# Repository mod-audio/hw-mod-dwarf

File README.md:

# hw-mod-dwarf

This repository contains the schematics and PCB design files for the MOD Dwarf hardware.

These files were created and can be improved with KiCAD, a free software Electronics CAD which is available at http://www.kicad.org/

This project should work with last revision of KiCad libraries and footprints available at https://github.com/KiCad/

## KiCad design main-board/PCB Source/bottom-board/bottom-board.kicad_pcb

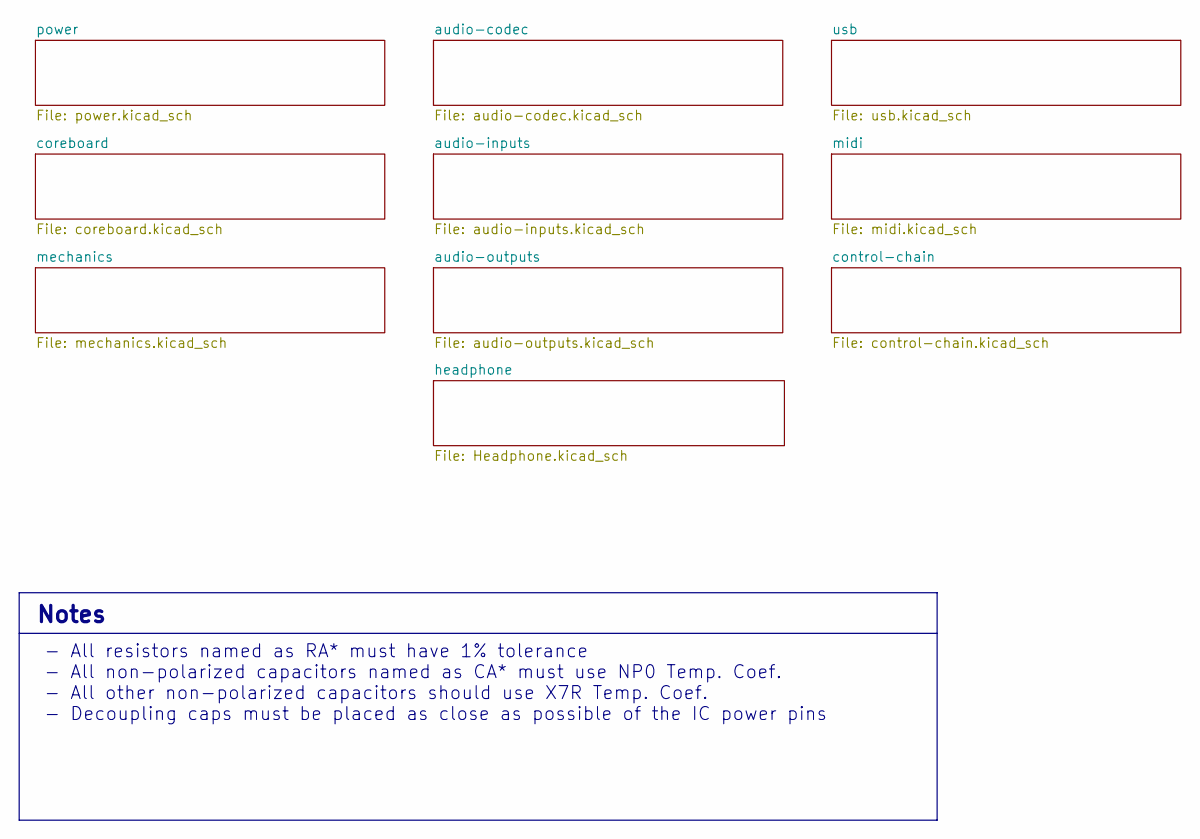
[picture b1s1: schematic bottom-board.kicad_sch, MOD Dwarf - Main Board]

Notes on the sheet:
- All resistors named as RA* must have 1% tolerance - All non-polarized capacitors named as CA* must use NP0 Temp. Coef. - All other non-polarized capacitors should use X7R Temp. Coef. - Decoupling caps must be placed as close as possible of the IC power pins
Notes

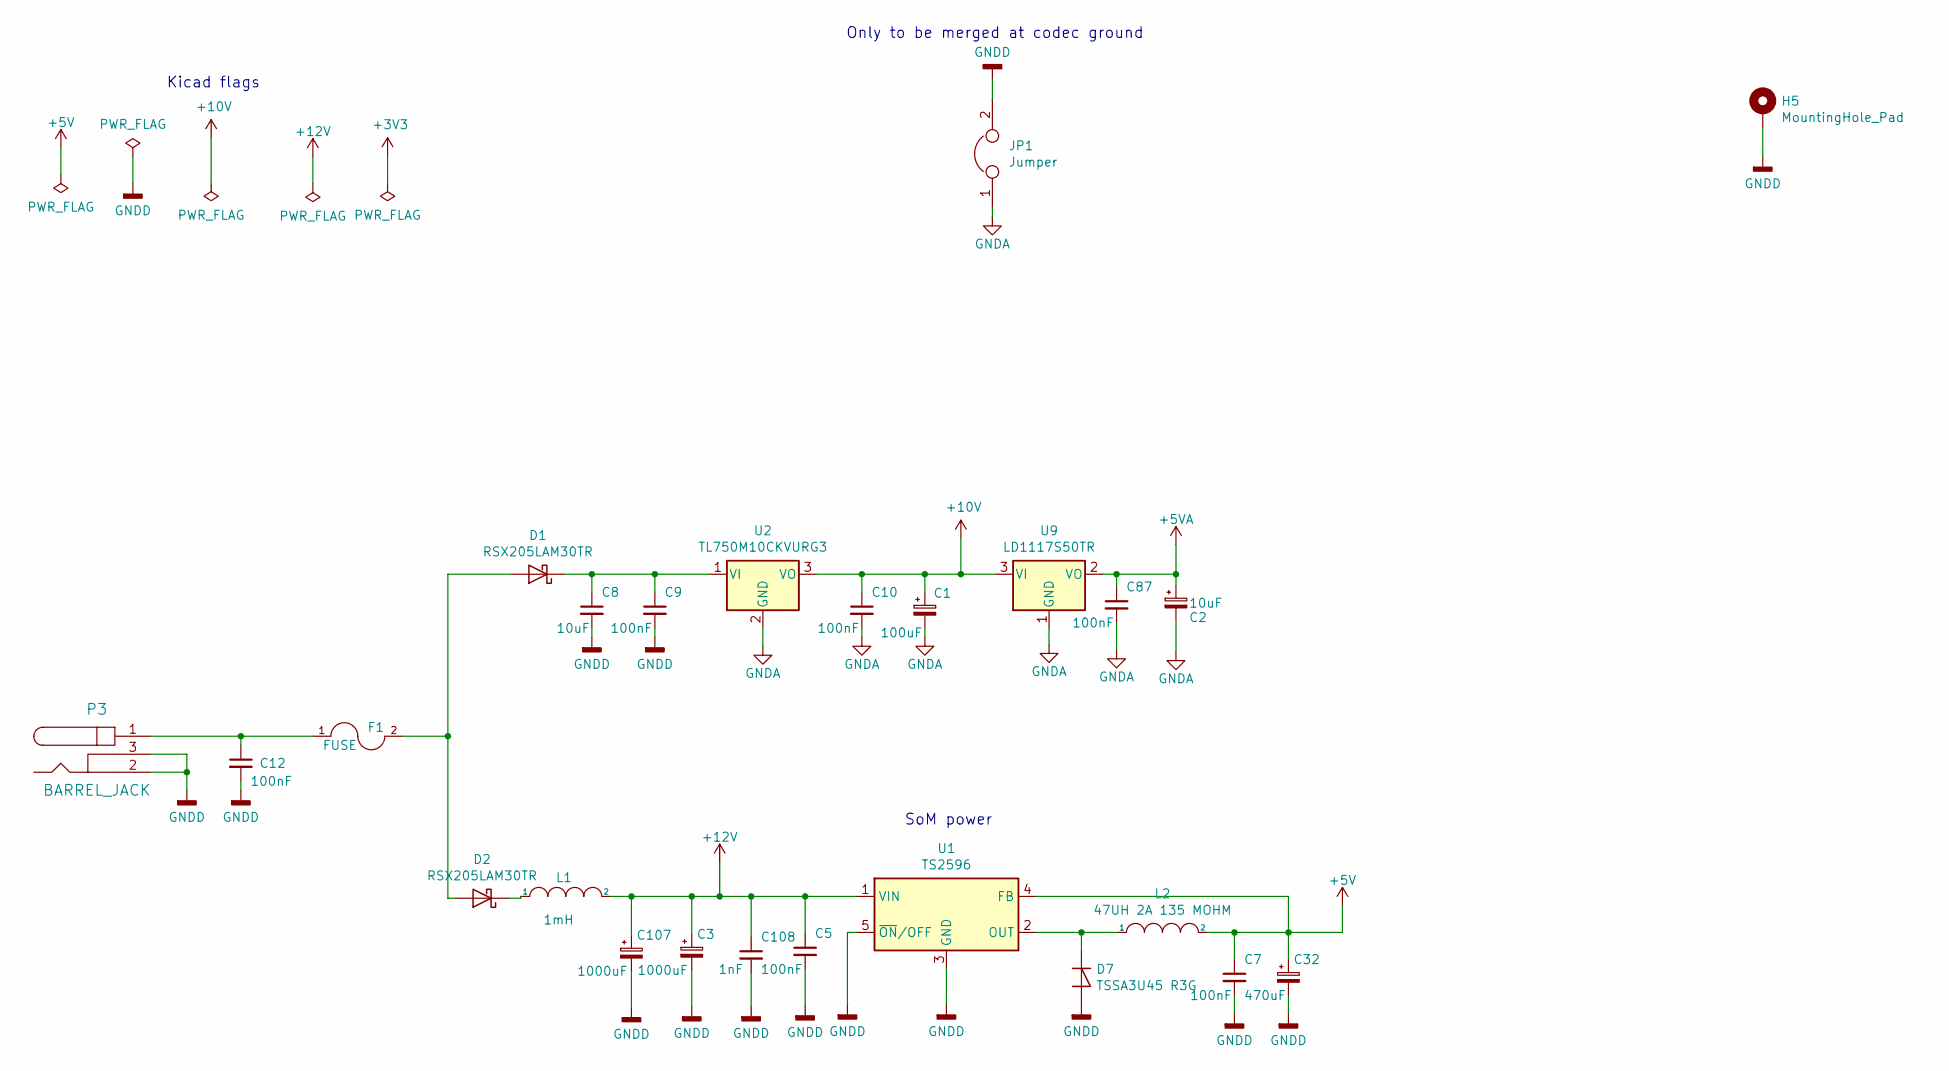
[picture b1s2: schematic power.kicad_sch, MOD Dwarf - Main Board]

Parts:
C1: 100uF; CP_Elec_6.3x7.7; MPN 107SML016M
C2: 10uF; CP_Elec_4x5.7; MPN EEE-HB1C100R
C3, C107: 1000uF; CP_Elec_10x10.5; MPN UCM1C102MNL1GS
C5, C7, C9, C10, C12, C87: 100nF; C_0603_1608Metric; MPN GCM188R71C104KA37D
C8: 10uF; C_0805_2012Metric; MPN GRM219R61E106KA12D
C32: 470uF; CP_Elec_8x10.5; MPN UCW1C471MNL1GS
C108: 1nF; C_0603_1608Metric; MPN C0603X7R500-103KNP
D1, D2: RSX205LAM30TR; D_SOD-128; MPN RSX205LAM30TR
D7: TSSA3U45 R3G; D_MELF; MPN TSSA3U45 R3G
F1: FUSE; Fuse_2920_7451Metric; MPN 0ZCF0200FF2C
H5: MountingHole_Pad; MountingHole_3.2mm_M3_DIN965_Pad
JP1: Jumper; SolderJumper-2_P1.3mm_Bridged2Bar_RoundedPad1.0x1.5mm
L1: 1mH; L_Bourns_SRR1260; MPN SRR1260-102K
L2: 47UH 2A 135 MOHM; SRN8040TA; MPN SRN8040TA-470M
P3: BARREL_JACK; BarrelJack_Horizontal; MPN PJ-002AH
U1: TS2596; TO-263-5_TabPin3; MPN TS2596CM550 RNG
U2: TL750M10CKVURG3; TO-252-3_TabPin2; MPN TL750M10CKVURG3
U9: LD1117S50TR; SOT-223-3_TabPin2; MPN LD1117S50TR

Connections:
+5V: C7.1, C32.1, L2.2, U1.4 (FB); also elsewhere on the board
+5VA: C2.1, C87.1, U9.2 (VO); also elsewhere on the board
+10V: C1.1, C10.1, U2.3 (VO), U9.3 (VI); also elsewhere on the board
+12V: C3.1, C5.1, C107.1, C108.1, L1.2, U1.1 (VIN); also elsewhere on the board
GNDA: C1.2, C2.2, C10.2, C87.2, JP1.1, U2.2 (GND), U9.1 (GND); also elsewhere on the board
GNDD: C3.2, C5.2, C7.2, C8.2, C9.2, C12.2, C32.2, C107.2, C108.2, D7.2 (A), H5.1, JP1.2, P3.2, P3.3, U1.3 (GND), U1.5 (~ON/OFF); also elsewhere on the board
unnamed: C8.1, C9.1, D1.1 (K), U2.1 (VI)
unnamed: C12.1, F1.1, P3.1
unnamed: D1.2 (A), D2.2 (A), F1.2
unnamed: D2.1 (K), L1.1
unnamed: D7.1 (K), L2.1, U1.2 (OUT)

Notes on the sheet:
SoM power
Only to be merged at codec ground
Kicad flags

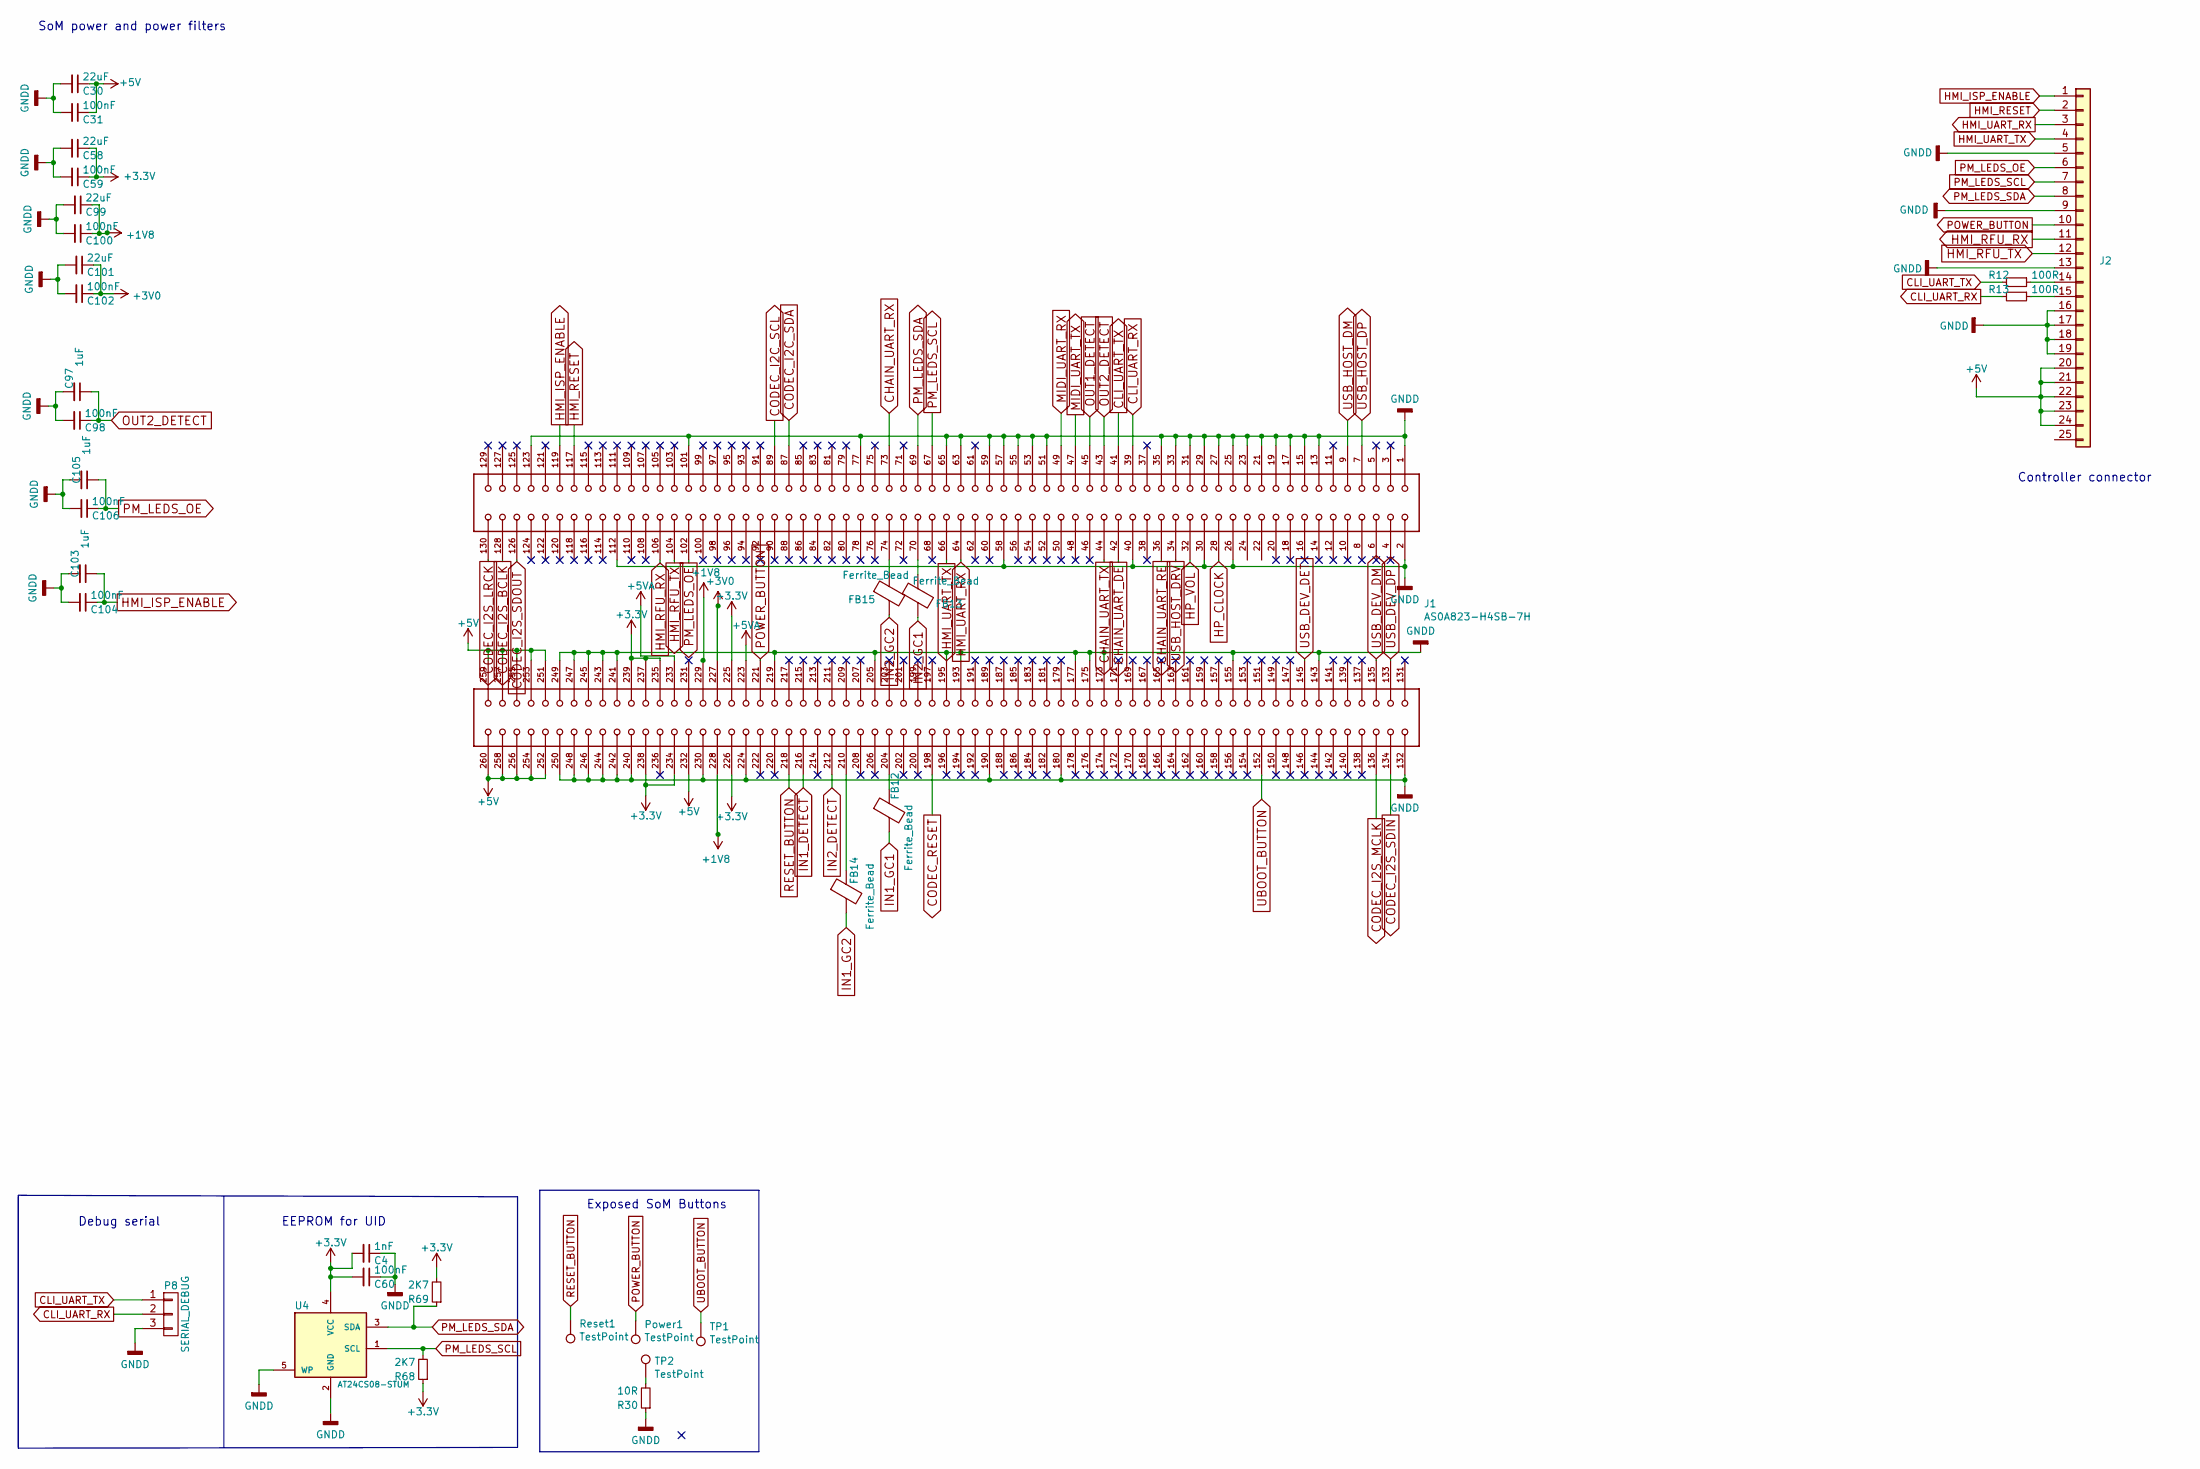
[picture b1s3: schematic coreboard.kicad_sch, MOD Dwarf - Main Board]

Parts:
C4: 1nF; C_0603_1608Metric; MPN C0603X7R500-103KNP
C30, C58, C99, C101: 22uF; C_0805_2012Metric; MPN CL21A226MPQNNNE
C31, C59, C60, C98, C100, C102, C104, C106: 100nF; C_0603_1608Metric; MPN GCM188R71C104KA37D
C97, C103, C105: 1uF; C_0603_1608Metric; MPN TMK107B7105KA-T
FB12, FB13, FB14, FB15: Ferrite_Bead; R_0603_1608Metric; MPN BLM18HD102SH1D
J1: AS0A823-H4SB-7H; TE_2309409-1; MPN TE_2309409-1
J2: MPN F51L-1A7H1-11024
P8: SERIAL_DEBUG; PinHeader_1x03_P2.54mm_Vertical; MPN DO NOT PLACE
Power1: TestPoint; TestPoint_Pad_D1.5mm
R12, R13: 100R; R_0603_1608Metric; MPN RT0603DRD07100RL
R30: 10R; R_0603_1608Metric; MPN CRGCQ0603J10R
R68, R69: 2K7; R_0603_1608Metric; MPN CRGCQ0603F2K7
Reset1: TestPoint; TestPoint_Pad_D1.5mm
TP1, TP2: TestPoint; TestPoint_Loop_D1.80mm_Drill1.0mm_Beaded
U4: AT24CS08-STUM; SOT-23-5; MPN AT24CS08-STUM

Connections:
+1V8: C99.1, C100.1, J1.228, J1.229
+3V0: C101.1, C102.1, J1.227
+5V: C30.1, C31.1, J1.232, J1.251, J1.252, J1.253, J1.254, J1.255, J1.256, J1.257, J1.258, J1.259, J1.260, J2.20, J2.21, J2.22, J2.23, J2.24; also elsewhere on the board
+5VA: J1.223, J1.233; also elsewhere on the board
CHAIN_UART_DE: J1.42; also elsewhere on the board
CHAIN_UART_RE: J1.36; also elsewhere on the board
CHAIN_UART_RX: J1.73; also elsewhere on the board
CHAIN_UART_TX: J1.44; also elsewhere on the board
CLI_UART_RX: J1.39, P8.2, R13.2
CLI_UART_TX: J1.41, P8.1, R12.2
CODEC_I2C_SCL: J1.89; also elsewhere on the board
CODEC_I2C_SDA: J1.87; also elsewhere on the board
CODEC_I2S_BCLK: J1.128; also elsewhere on the board
CODEC_I2S_LRCK: J1.130; also elsewhere on the board
CODEC_I2S_MCLK: J1.136; also elsewhere on the board
CODEC_I2S_SDIN: J1.134; also elsewhere on the board
CODEC_I2S_SDOUT: J1.126; also elsewhere on the board
CODEC_RESET: J1.198; also elsewhere on the board
GNDD: C4.1, C30.2, C31.2, C58.2, C59.2, C60.1, C97.2, C98.2, C99.2, C100.2, C101.2, C102.2, C103.2, C104.2, C105.2, C106.2, J1.1, J1.2, J1.13, J1.15, J1.17, J1.19, J1.21, J1.23, J1.25, J1.26, J1.27, J1.29, J1.30, J1.31, J1.33, J1.35, J1.40, J1.51, J1.53, J1.55, J1.57, J1.58, J1.59, J1.63, J1.65, J1.77, J1.101, J1.112, J1.123, J1.132, J1.143, J1.155, J1.173, J1.175, J1.177, J1.180, J1.190, J1.193, J1.195, J1.205, J1.219, J1.224, J1.230, J1.240, J1.241, J1.242, J1.243, J1.244, J1.245, J1.246, J1.247, J1.248, J1.249, J1.250, J2.5, J2.9, J2.13, J2.16, J2.17, J2.18, J2.19, P8.3, R30.1, U4.2 (GND), U4.5 (WP); also elsewhere on the board
HMI_ISP_ENABLE: C103.1, C104.1, J1.119, J2.1; also elsewhere on the board
HMI_RESET: J1.117, J2.2; also elsewhere on the board
HMI_RFU_RX: J1.106, J2.11; also elsewhere on the board
HMI_RFU_TX: J1.104, J2.12; also elsewhere on the board
HMI_UART_RX: J1.64, J2.3; also elsewhere on the board
HMI_UART_TX: J1.66, J2.4; also elsewhere on the board
HP_CLOCK: J1.28; also elsewhere on the board
HP_VOL: J1.32; also elsewhere on the board
IN1_DETECT: J1.216; also elsewhere on the board
IN1_GC1: FB12.2; also elsewhere on the board
IN1_GC2: FB14.2; also elsewhere on the board
IN2_DETECT: J1.212; also elsewhere on the board
IN2_GC1: FB13.2; also elsewhere on the board
IN2_GC2: FB15.2; also elsewhere on the board
MIDI_UART_RX: J1.49; also elsewhere on the board
MIDI_UART_TX: J1.47; also elsewhere on the board
unnamed: FB12.1, J1.204
unnamed: FB13.1, J1.70
unnamed: FB14.1, J1.210
unnamed: FB15.1, J1.74
unnamed 122: J2.14, R12.1; also elsewhere on the board
unnamed 123: J2.15, R13.1; also elsewhere on the board
unnamed: R30.2, TP2.1
OUT1_DETECT: J1.45; also elsewhere on the board
OUT2_DETECT: C97.1, C98.1, J1.43; also elsewhere on the board
PM_LEDS_OE: C105.1, C106.1, J1.102, J2.6; also elsewhere on the board
PM_LEDS_SCL: J1.67, J2.7, R68.2, U4.1 (SCL); also elsewhere on the board
PM_LEDS_SDA: J1.69, J2.8, R69.1, U4.3 (SDA); also elsewhere on the board
POWER_BUTTON: J1.221, J2.10, Power1.1; also elsewhere on the board
RESET_BUTTON: J1.218, Reset1.1; also elsewhere on the board
UBOOT_BUTTON: J1.152, TP1.1
USB_DEV_DET: J1.145; also elsewhere on the board
USB_DEV_DM: J1.135; also elsewhere on the board
USB_DEV_DP: J1.133; also elsewhere on the board
USB_HOST_DM: J1.9; also elsewhere on the board
USB_HOST_DP: J1.7; also elsewhere on the board
USB_HOST_DRV: J1.34; also elsewhere on the board

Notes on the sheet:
SoM power and power filters
Debug serial
Exposed SoM Buttons
EEPROM for UID
Controller connector

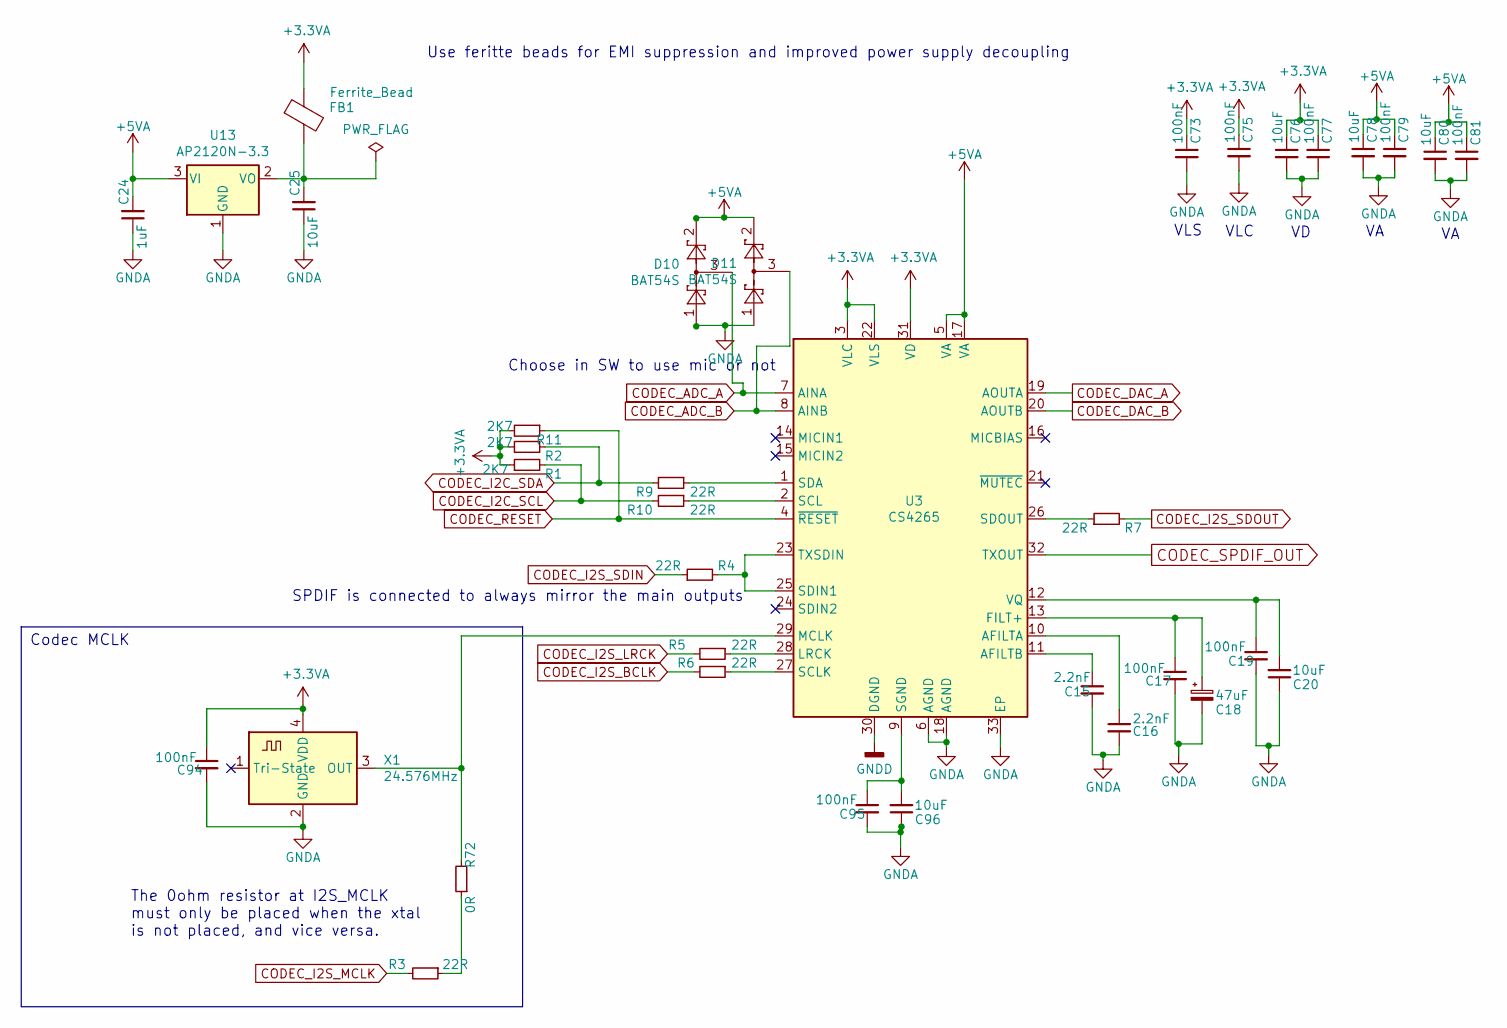
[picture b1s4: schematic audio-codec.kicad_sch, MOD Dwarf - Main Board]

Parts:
C15, C16: 2.2nF; C_0603_1608Metric; MPN GRM1885C1H222JA01D
C17, C19, C73, C75, C77, C79, C81, C94, C95: 100nF; C_0603_1608Metric; MPN GCM188R71C104KA37D
C18: 47uF; CP_Elec_5x5.4; MPN EDK476M016A9DAA
C20, C25, C76, C78, C80, C96: 10uF; C_0805_2012Metric; MPN GRM219R61E106KA12D
C24: 1uF; C_0603_1608Metric; MPN TMK107B7105KA-T
D10, D11: BAT54S; SOT-23; MPN BAT54SFILM
FB1: Ferrite_Bead; R_0603_1608Metric; MPN BLM18HD102SH1D
R1, R2, R11: 2K7; R_0603_1608Metric; MPN CRGCQ0603F2K7
R3, R4, R5, R6, R7, R9, R10: 22R; R_0603_1608Metric; MPN RMCF0603JT22R0
R72: 0R; R_0603_1608Metric; MPN RMCF0603ZT0R00
U3: CS4265; QFN-32-1EP_5x5mm_P0.5mm_EP3.1x3.1mm; MPN CS4265-CNZ
U13: AP2120N-3.3; SOT-23; MPN AP2120N-3.3TRG1
X1: 24.576MHz; Oscillator_SMD_Abracon_ASV-4Pin_7.0x5.1mm; MPN DO NOT PLACE

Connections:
+3.3VA: C73.1, C75.1, C76.1, C77.1, C94.1, FB1.1, R1.1, R2.2, R11.2, U3.3 (VLC), U3.22 (VLS), U3.31 (VD), X1.4 (VDD)
+5VA: C24.2, C78.1, C79.1, C80.1, C81.1, D10.2, D11.2, U3.5 (VA), U3.17 (VA), U13.3 (VI); also elsewhere on the board
CODEC_ADC_A: D10.3, U3.7 (AINA); also elsewhere on the board
CODEC_ADC_B: D11.3, U3.8 (AINB); also elsewhere on the board
CODEC_DAC_A: U3.19 (AOUTA); also elsewhere on the board
CODEC_DAC_B: U3.20 (AOUTB); also elsewhere on the board
CODEC_I2C_SCL: R1.2, R10.2; also elsewhere on the board
CODEC_I2C_SDA: R2.1, R9.2; also elsewhere on the board
CODEC_I2S_BCLK: R6.2; also elsewhere on the board
CODEC_I2S_LRCK: R5.2; also elsewhere on the board
CODEC_I2S_MCLK: R3.2; also elsewhere on the board
CODEC_I2S_SDIN: R4.1; also elsewhere on the board
CODEC_I2S_SDOUT: R7.2; also elsewhere on the board
CODEC_RESET: R11.1, U3.4 (~RESET); also elsewhere on the board
GNDA: C15.2, C16.2, C17.2, C18.2, C19.2, C20.1, C24.1, C25.1, C73.2, C75.2, C76.2, C77.2, C78.2, C79.2, C80.2, C81.2, C94.2, C95.2, C96.1, D10.1, D11.1, U3.6 (AGND), U3.18 (AGND), U3.33 (EP), U13.1 (GND), X1.2 (GND); also elsewhere on the board
GNDD: U3.30 (DGND); also elsewhere on the board
unnamed: C15.1, U3.11 (AFILTB)
unnamed: C16.1, U3.10 (AFILTA)
unnamed: C17.1, C18.1, U3.13 (FILT+)
unnamed: C19.1, C20.2, U3.12 (VQ)
unnamed: C25.2, FB1.2, U13.2 (VO)
unnamed: C95.1, C96.2, U3.9 (SGND)
unnamed: R3.1, R72.1
unnamed: R4.2, U3.23 (TXSDIN), U3.25 (SDIN1)
unnamed: R5.1, U3.28 (LRCK)
unnamed: R6.1, U3.27 (SCLK)
unnamed: R7.1, U3.26 (SDOUT)
unnamed: R9.1, U3.1 (SDA)
unnamed: R10.1, U3.2 (SCL)
unnamed: R72.2, U3.29 (MCLK), X1.3 (OUT)

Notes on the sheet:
Use feritte beads for EMI suppression and improved power supply decoupling
VLS
Choose in SW to use mic or not
Codec MCLK
VLC
SPDIF is connected to always mirror the main outputs
The 0ohm resistor at I2S_MCLK must only be placed when the xtal is not placed, and vice versa.

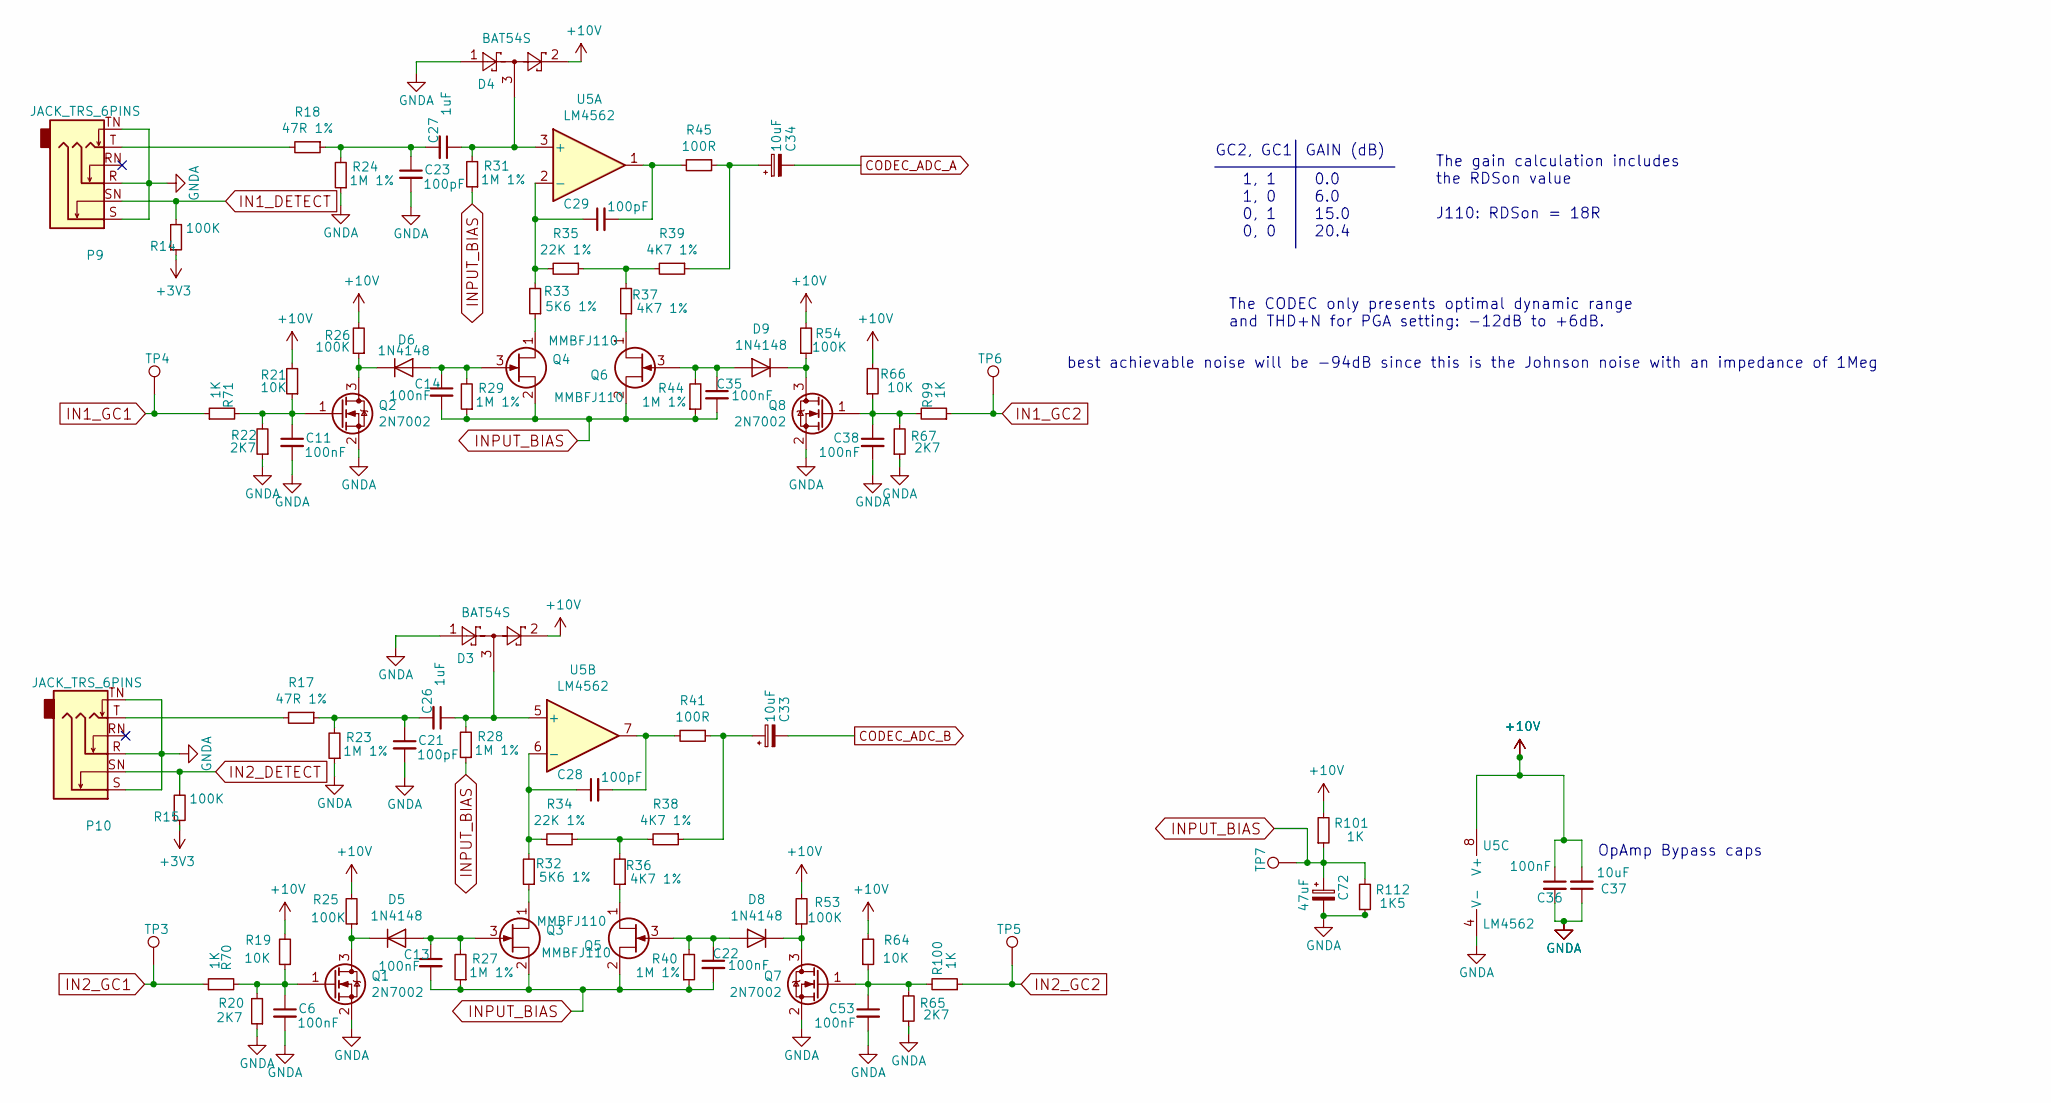
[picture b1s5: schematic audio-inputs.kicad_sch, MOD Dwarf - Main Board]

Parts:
C6, C11, C13, C14, C22, C35, C36, C38, C53: 100nF; C_0603_1608Metric; MPN GCM188R71C104KA37D
C21, C23, C28, C29: 100pF; C_0603_1608Metric; MPN C0603C101J3GACTU
C26, C27: 1uF; C_0603_1608Metric; MPN TMK107B7105KA-T
C33, C34: 10uF; CP_Elec_4x5.7; MPN EEE-HB1C100R
C37: 10uF; C_0805_2012Metric; MPN GRM219R61E106KA12D
C72: 47uF; CP_Elec_5x5.4; MPN EDK476M016A9DAA
D3, D4: BAT54S; SOT-23; MPN BAT54SFILM
D5, D6, D8, D9: 1N4148; D_SOD-323; MPN 1N4148WS
P9, P10: JACK_TRS_6PINS; Jack_3.5mm_Neutrik_NMJ6HCD2_Horizontal; MPN NYS215
Q1, Q2, Q7, Q8: 2N7002; SOT-23; MPN 2N7002P,215
Q3, Q4, Q5, Q6: MMBFJ110; SOT-23; MPN MMBFJ110
R14, R15, R25, R26, R53, R54: 100K; R_0603_1608Metric; MPN RMCF0603JT100K
R17, R18: 47R 1%; R_0603_1608Metric; MPN RT0603DRE0747RL
R19, R21, R64, R66: 10K; R_0603_1608Metric; MPN RR0816P-103-D
R20, R22, R65, R67: 2K7; R_0603_1608Metric; MPN CRGCQ0603F2K7
R23, R24, R27, R28, R29, R31, R40, R44: 1M 1%; R_0603_1608Metric; MPN RT0603BRD071ML
R32, R33: 5K6 1%; R_0603_1608Metric; MPN ERA-3AED562V
R34, R35: 22K 1%; R_0603_1608Metric; MPN RT0603DRD0722KL
R36, R37, R38, R39: 4K7 1%; R_0603_1608Metric; MPN RT0603DRE074K7L
R41, R45: 100R; R_0603_1608Metric; MPN RT0603DRD07100RL
R70, R71, R99, R100, R101: 1K; R_0603_1608Metric; MPN ERJ-PB3D1001V
R112: 1K5; R_0603_1608Metric
TP3, TP4, TP5, TP6: TestPoint; TestPoint_Pad_D1.0mm
TP7: TestPoint; TestPoint_Pad_D2.0mm
U5: LM4562; SOIC-8_3.9x4.9mm_P1.27mm; MPN LM4562MAX/NOPB

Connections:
+10V: C36.1, C37.2, D3.2, D4.2, R19.2, R21.2, R25.2, R26.2, R53.2, R54.2, R64.2, R66.2, R101.2, U5.8 (V+); also elsewhere on the board
CODEC_ADC_A: C34.2; also elsewhere on the board
CODEC_ADC_B: C33.2; also elsewhere on the board
GNDA: C6.2, C11.2, C21.2, C23.2, C36.2, C37.1, C38.2, C53.2, C72.2, D3.1, D4.1, P9.R, P9.S, P9.TN, P10.R, P10.S, P10.TN, Q1.2 (S), Q2.2 (S), Q7.2 (S), Q8.2 (S), R20.1, R22.1, R23.1, R24.1, R65.1, R67.1, R112.1, U5.4 (V-); also elsewhere on the board
IN1_DETECT: P9.SN, R14.2; also elsewhere on the board
IN1_GC1: R71.1, TP4.1; also elsewhere on the board
IN1_GC2: R99.1, TP6.1; also elsewhere on the board
IN2_DETECT: P10.SN, R15.2; also elsewhere on the board
IN2_GC1: R70.1, TP3.1; also elsewhere on the board
IN2_GC2: R100.1, TP5.1; also elsewhere on the board
INPUT_BIAS: C13.2, C14.2, C22.2, C35.2, C72.1, Q3.2 (S), Q4.2 (S), Q5.2 (S), Q6.2 (S), R27.1, R28.1, R29.1, R31.1, R40.1, R44.1, R101.1, R112.2, TP7.1
unnamed: C6.1, Q1.1 (G), R19.1, R20.2, R70.2
unnamed: C11.1, Q2.1 (G), R21.1, R22.2, R71.2
unnamed: C13.1, D5.2 (A), Q3.3 (G), R27.2
unnamed: C14.1, D6.2 (A), Q4.3 (G), R29.2
unnamed: C21.1, C26.2, R17.1, R23.2
unnamed: C22.1, D8.2 (A), Q5.3 (G), R40.2
unnamed: C23.1, C27.2, R18.1, R24.2
unnamed: C26.1, D3.3, R28.2, U5.5 (+)
unnamed: C27.1, D4.3, R31.2, U5.3 (+)
unnamed: C28.1, R32.2, R34.2, U5.6 (-)
unnamed: C28.2, R41.2, U5.7
unnamed: C29.1, R33.2, R35.2, U5.2 (-)
unnamed: C29.2, R45.2, U5.1
unnamed: C33.1, R38.1, R41.1
unnamed: C34.1, R39.1, R45.1
unnamed: C35.1, D9.2 (A), Q6.3 (G), R44.2
unnamed: C38.1, Q8.1 (G), R66.1, R67.2, R99.2
unnamed: C53.1, Q7.1 (G), R64.1, R65.2, R100.2
unnamed: D5.1 (K), Q1.3 (D), R25.1
unnamed: D6.1 (K), Q2.3 (D), R26.1
unnamed: D8.1 (K), Q7.3 (D), R53.1
unnamed: D9.1 (K), Q8.3 (D), R54.1
unnamed: P9.T, R18.2
unnamed: P10.T, R17.2
unnamed: Q3.1 (D), R32.1
unnamed: Q4.1 (D), R33.1
unnamed: Q5.1 (D), R36.1
unnamed: Q6.1 (D), R37.1
unnamed: R34.1, R36.2, R38.2
unnamed: R35.1, R37.2, R39.2

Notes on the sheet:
best achievable noise will be -94dB since this is the Johnson noise with an impedance of 1Meg
The CODEC only presents optimal dynamic range and THD+N for PGA setting: -12dB to +6dB.
OpAmp Bypass caps
The gain calculation includes the RDSon value J110: RDSon = 18R
1, 1 1, 0 0, 1 0, 0
GAIN (dB)
0.0 6.0 15.0 20.4
GC2, GC1

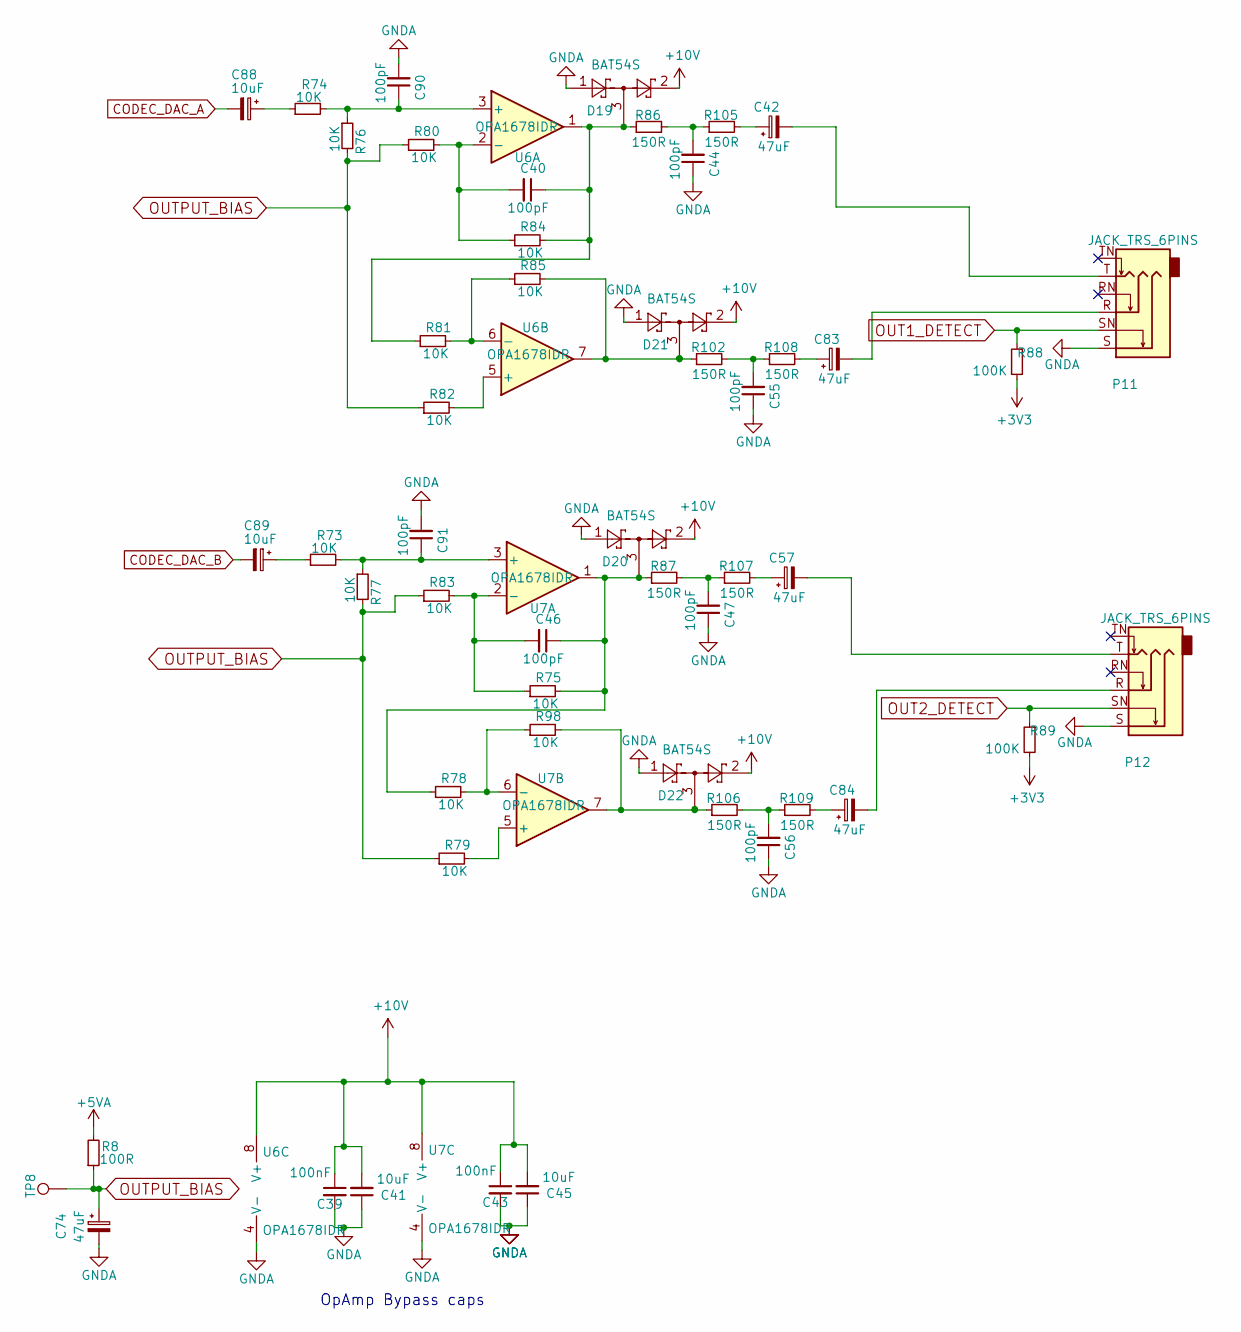
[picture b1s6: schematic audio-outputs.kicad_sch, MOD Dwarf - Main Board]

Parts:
C39, C43: 100nF; C_0603_1608Metric; MPN GCM188R71C104KA37D
C40, C44, C46, C47, C55, C56, C90, C91: 100pF; C_0603_1608Metric; MPN C0603C101J3GACTU
C41, C45: 10uF; C_0805_2012Metric; MPN GRM219R61E106KA12D
C42, C57, C74, C83, C84: 47uF; CP_Elec_5x5.4; MPN EDK476M016A9DAA
C88, C89: 10uF; CP_Elec_4x5.7; MPN EEE-HB1C100R
D19, D20, D21, D22: BAT54S; SOT-23; MPN BAT54SFILM
P11, P12: JACK_TRS_6PINS; Jack_3.5mm_Neutrik_NMJ6HCD2_Horizontal; MPN NYS215
R8: 100R; R_0603_1608Metric; MPN RT0603DRD07100RL
R73, R74, R75, R76, R77, R78, R79, R80, R81, R82, R83, R84, R85, R98: 10K; R_0603_1608Metric; MPN RR0816P-103-D
R86, R87, R102, R105, R106, R107, R108, R109: 150R; R_0603_1608Metric; MPN RC0603FR-07150RL
R88, R89: 100K; R_0603_1608Metric; MPN RMCF0603JT100K
TP8: TestPoint; TestPoint_Pad_D2.0mm
U6, U7: OPA1678IDR; SOIC-8_3.9x4.9mm_P1.27mm; MPN OPA1678IDR

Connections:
+5VA: R8.2; also elsewhere on the board
+10V: C39.1, C41.2, C43.1, C45.2, D19.2, D20.2, D21.2, D22.2, U6.8 (V+), U7.8 (V+); also elsewhere on the board
CODEC_DAC_A: C88.2; also elsewhere on the board
CODEC_DAC_B: C89.2; also elsewhere on the board
GNDA: C39.2, C41.1, C43.2, C44.1, C45.1, C47.1, C55.1, C56.1, C74.2, C90.2, C91.2, D19.1, D20.1, D21.1, D22.1, P11.S, P12.S, U6.4 (V-), U7.4 (V-); also elsewhere on the board
unnamed: C40.1, D19.3, R81.1, R84.2, R86.1, U6.1
unnamed: C40.2, R80.2, R84.1, U6.2 (-)
unnamed: C42.1, R105.2
unnamed: C42.2, P11.T
unnamed: C44.2, R86.2, R105.1
unnamed: C46.1, D20.3, R75.2, R78.1, R87.1, U7.1
unnamed: C46.2, R75.1, R83.2, U7.2 (-)
unnamed: C47.2, R87.2, R107.1
unnamed: C55.2, R102.2, R108.1
unnamed: C56.2, R106.2, R109.1
unnamed: C57.1, R107.2
unnamed: C57.2, P12.T
unnamed: C83.1, R108.2
unnamed: C83.2, P11.R
unnamed: C84.1, R109.2
unnamed: C84.2, P12.R
unnamed: C88.1, R74.1
unnamed: C89.1, R73.1
unnamed: C90.1, R74.2, R76.1, U6.3 (+)
unnamed: C91.1, R73.2, R77.1, U7.3 (+)
unnamed: D21.3, R85.2, R102.1, U6.7
unnamed: D22.3, R98.2, R106.1, U7.7
unnamed: R78.2, R98.1, U7.6 (-)
unnamed: R79.2, U7.5 (+)
unnamed: R81.2, R85.1, U6.6 (-)
unnamed: R82.2, U6.5 (+)
OUT1_DETECT: P11.SN, R88.1; also elsewhere on the board
OUT2_DETECT: P12.SN, R89.1; also elsewhere on the board
OUTPUT_BIAS: C74.1, R8.1, R76.2, R77.2, R79.1, R80.1, R82.1, R83.1, TP8.1

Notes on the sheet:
OpAmp Bypass caps

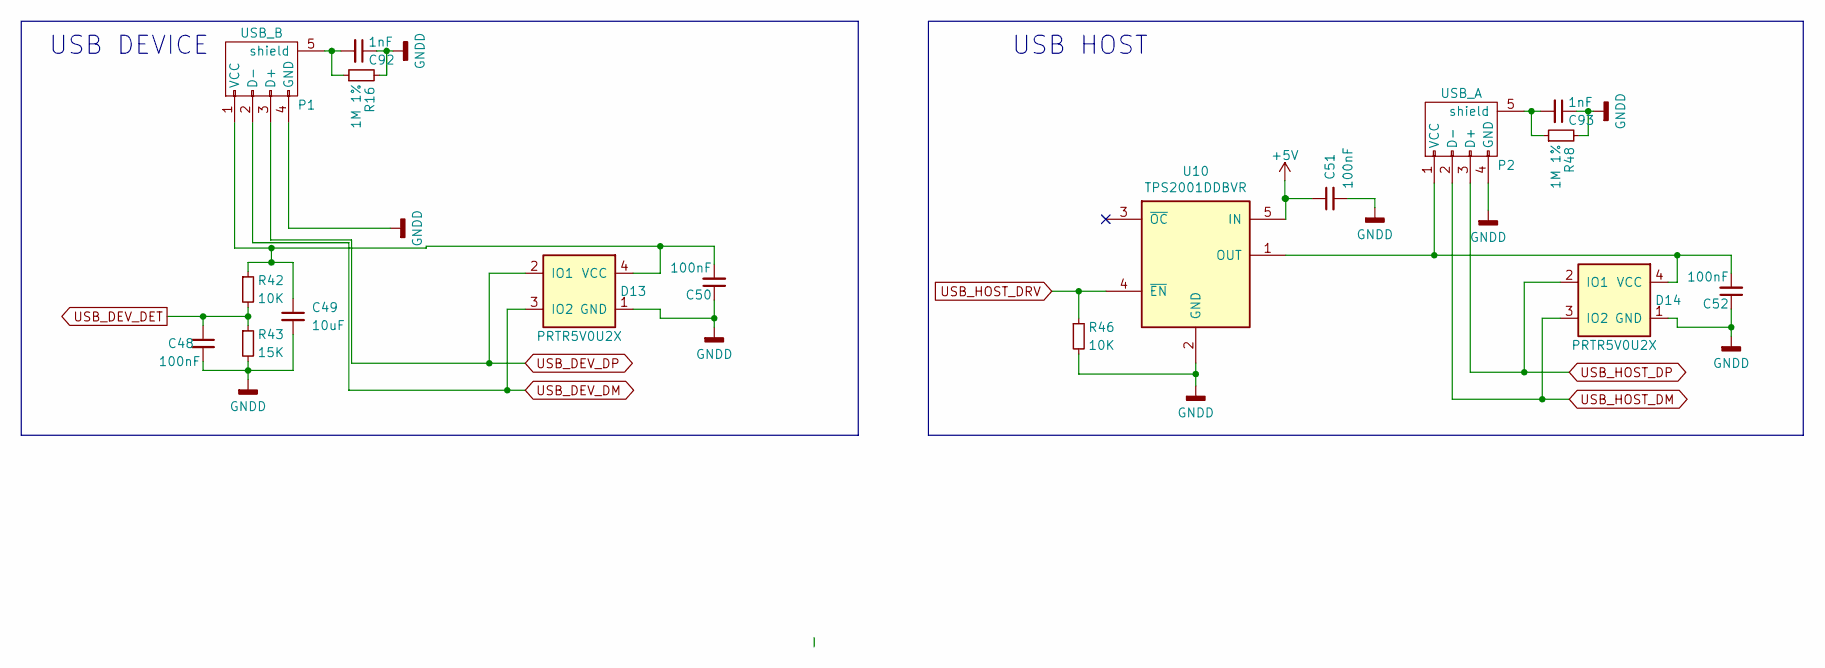
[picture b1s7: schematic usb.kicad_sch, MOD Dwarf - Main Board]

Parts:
C48, C50, C51, C52: 100nF; C_0603_1608Metric; MPN GCM188R71C104KA37D
C49: 10uF; C_0805_2012Metric; MPN GRM219R61E106KA12D
C92, C93: 1nF; C_0603_1608Metric; MPN C0603X7R500-103KNP
D13, D14: PRTR5V0U2X; SOT-143; MPN PRTR5V0U2X,215
P1: USB_B; USB_B_OST_USB-B1HSxx_Horizontal; MPN 61729-1011BLF
P2: USB_A; USB_A_Vertical; MPN KUSBX-SLAS1N-B
R16, R48: 1M 1%; R_0603_1608Metric; MPN RT0603BRD071ML
R42, R46: 10K; R_0603_1608Metric; MPN RR0816P-103-D
R43: 15K; R_0603_1608Metric; MPN RMCF0603JT15K0
U10: TPS2001DDBVR; SOT-23-5; MPN TPS2001DDBVR

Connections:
+5V: C51.1, U10.5 (IN); also elsewhere on the board
GNDD: C48.2, C49.2, C50.1, C51.2, C52.1, C92.1, C93.1, D13.1 (GND), D14.1 (GND), P1.4 (GND), P2.4 (GND), R16.2, R43.2, R46.2, R48.2, U10.2 (GND); also elsewhere on the board
unnamed: C49.1, C50.2, D13.4 (VCC), P1.1 (VCC), R42.1
unnamed: C52.2, D14.4 (VCC), P2.1 (VCC), U10.1 (OUT)
unnamed: C92.2, P1.5 (shield), R16.1
unnamed: C93.2, P2.5 (shield), R48.1
USB_DEV_DET: C48.1, R42.2, R43.1; also elsewhere on the board
USB_DEV_DM: D13.3 (IO2), P1.2 (D-); also elsewhere on the board
USB_DEV_DP: D13.2 (IO1), P1.3 (D+); also elsewhere on the board
USB_HOST_DM: D14.3 (IO2), P2.2 (D-); also elsewhere on the board
USB_HOST_DP: D14.2 (IO1), P2.3 (D+); also elsewhere on the board
USB_HOST_DRV: R46.1, U10.4 (~EN); also elsewhere on the board

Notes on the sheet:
USB DEVICE
USB HOST
